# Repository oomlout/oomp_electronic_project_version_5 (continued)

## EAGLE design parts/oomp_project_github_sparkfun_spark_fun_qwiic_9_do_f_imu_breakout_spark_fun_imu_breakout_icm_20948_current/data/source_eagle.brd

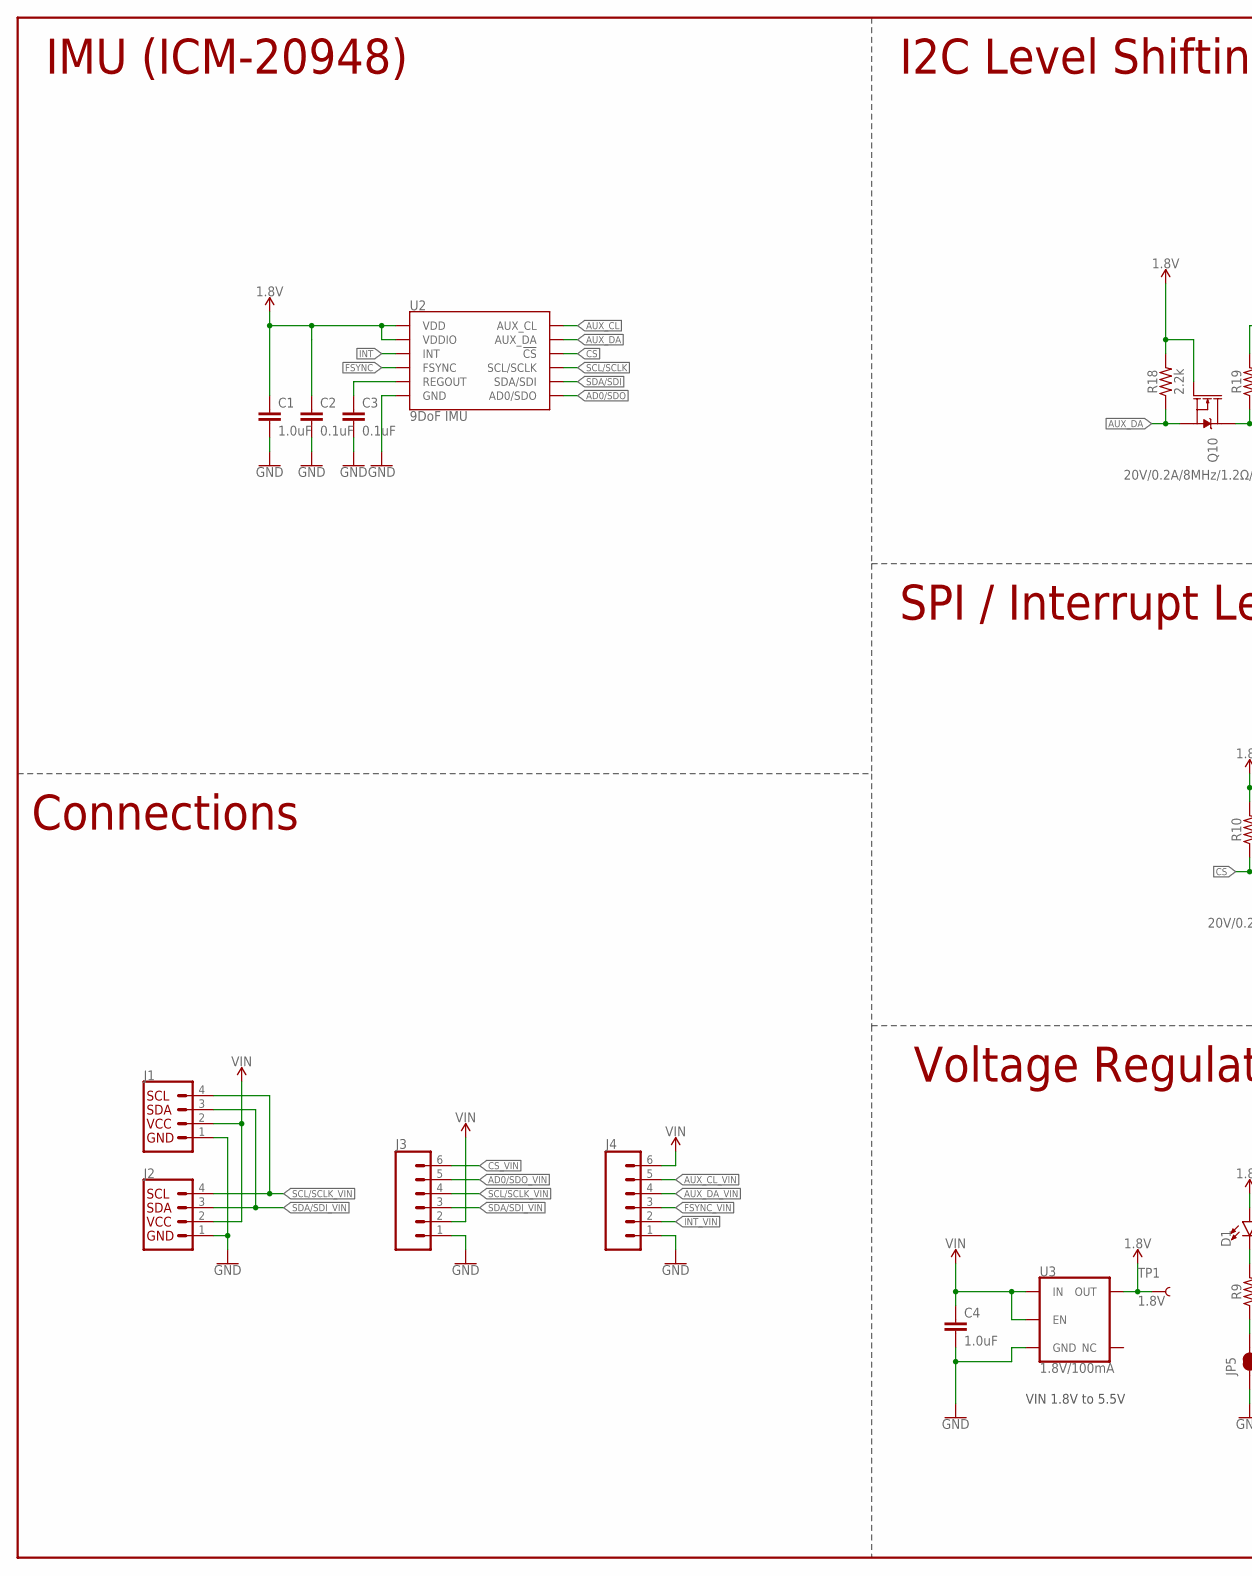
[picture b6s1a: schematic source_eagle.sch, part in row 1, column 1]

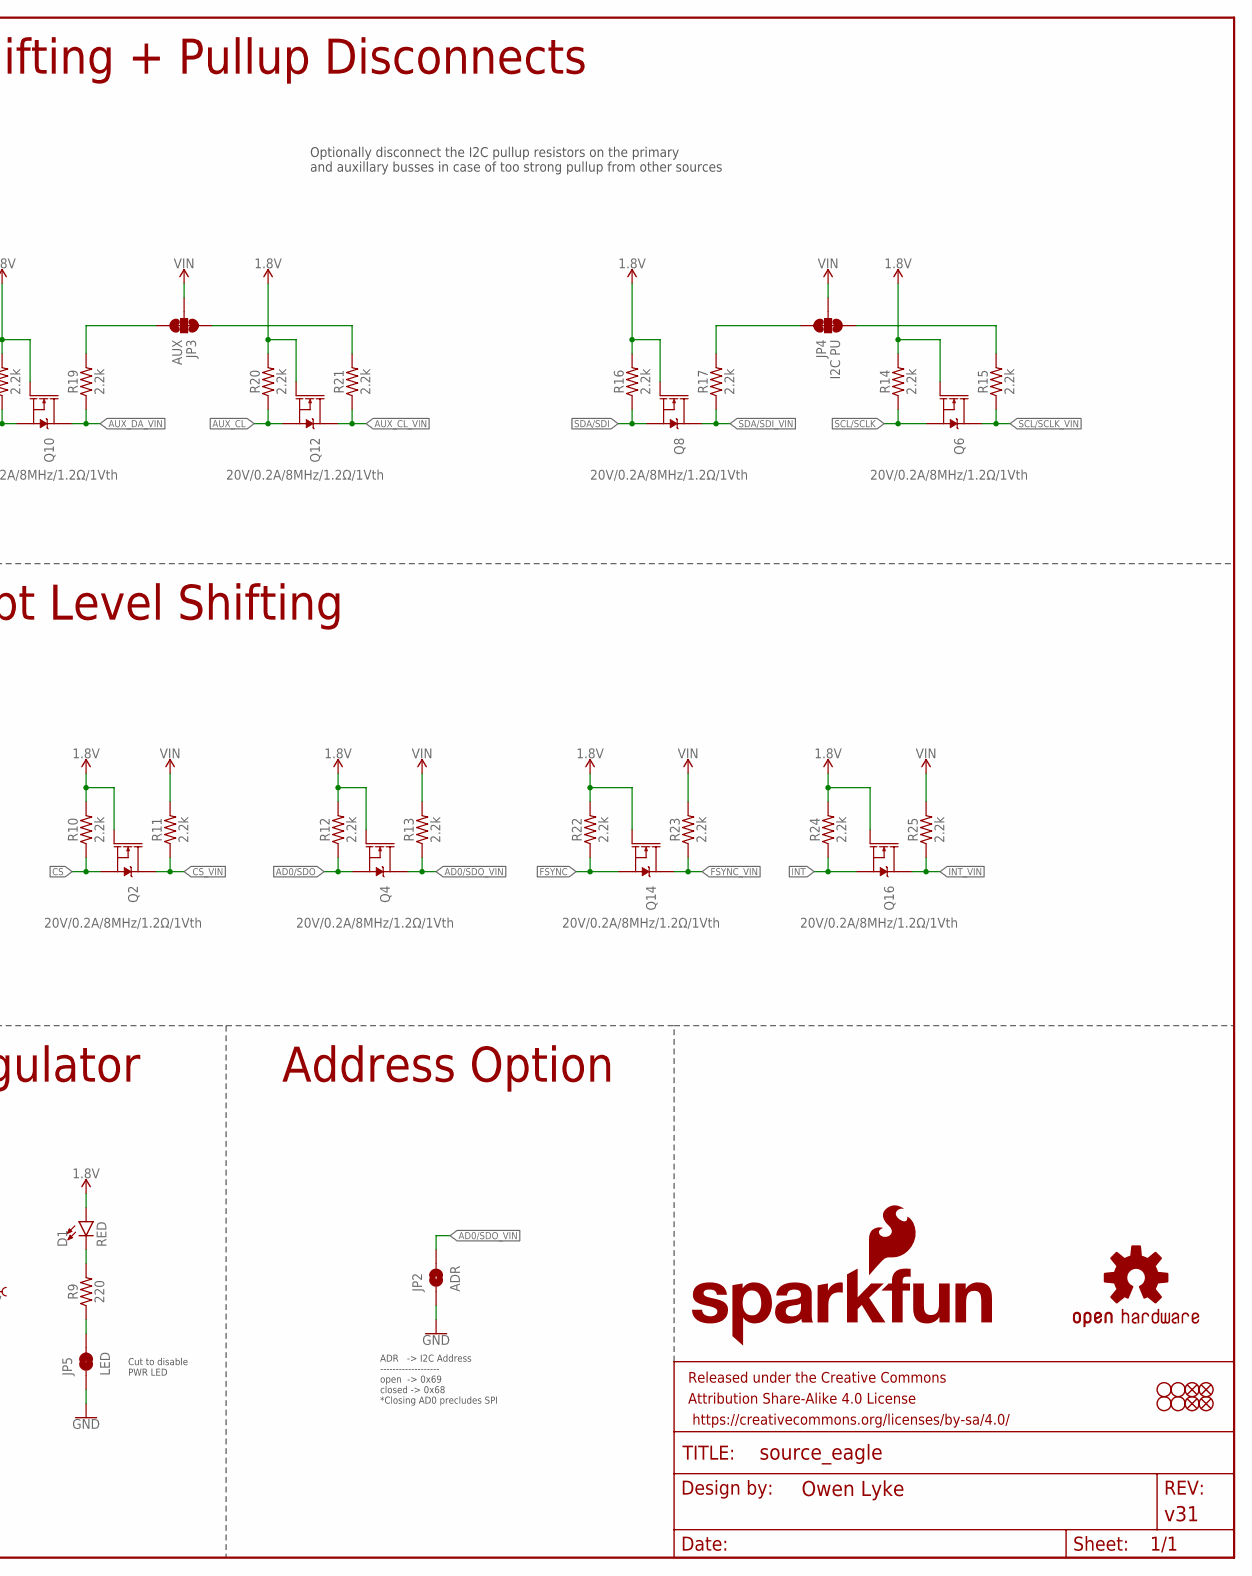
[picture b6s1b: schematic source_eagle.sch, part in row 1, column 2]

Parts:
C1, C4: 1.0uF; 0603
C2, C3: 0.1uF; 0603
D1: RED; LED-0603
FD1, FD2, FD3, FD4: FIDUCIAL1X2; FIDUCIAL-1X2
FRAME2: FRAME-LEDGER; CREATIVE_COMMONS
H1, H2, H3, H4: STAND-OFF
J1, J2: QWIIC_CONNECTORJS-1MM; JST04_1MM_RA
J3, J4: CONN_06NO_SILK_NO_POP; 1X06_NO_SILK
JP2: ADR; SMT-JUMPER_2_NO_SILK
JP3: AUX; SMT-JUMPER_3_2-NC_TRACE_SILK
JP4: I2C PU; SMT-JUMPER_3_2-NC_TRACE_SILK
JP5: LED; SMT-JUMPER_2_NC_TRACE_SILK
LOGO1: SFE_LOGO_NAME_FLAME.1_INCH; SFE_LOGO_NAME_FLAME_.1
LOGO2: OSHW-LOGOMINI; OSHW-LOGO-MINI
Q2, Q4, Q6, Q8, Q10, Q12, Q14, Q16: 20V/0.2A/8MHz/1.2Ω/1Vth; SOT-416FL
R9: 220; 0603
R10, R11, R12, R13, R14, R15, R16, R17, R18, R19, R20, R21, R22, R23, R24, R25: 2.2k; 0402-TIGHT
TP1: 1.8V; PAD.03X.03
U2: 9DoF IMU; QFN24-3X3
U3: 1.8V/100mA; SC70

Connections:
1.8V: C1.1, C2.1, D1.A, Q2.1 (G), Q4.1 (G), Q6.1 (G), Q8.1 (G), Q10.1 (G), Q12.1 (G), Q14.1 (G), Q16.1 (G), R10.2, R12.2, R14.2, R16.2, R18.2, R20.2, R22.2, R24.2, TP1.P$1, U2.8 (VDDIO), U2.13 (VDD), U3.5 (OUT)
!CS: Q2.2 (S), R10.1, U2.22 (!CS)
!CS!_VIN: J3.6, Q2.3 (D), R11.1
AD0/SDO: Q4.2 (S), R12.1, U2.9 (AD0/SDO)
AD0/SDO_VIN: J3.5, JP2.2, Q4.3 (D), R13.1
AUX_CL: Q12.2 (S), R20.1, U2.7 (AUX_CL)
AUX_CL_VIN: J4.5, Q12.3 (D), R21.1
AUX_DA: Q10.2 (S), R18.1, U2.21 (AUX_DA)
AUX_DA_VIN: J4.4, Q10.3 (D), R19.1
FSYNC: Q14.2 (S), R22.1, U2.11 (FSYNC)
FSYNC_VIN: J4.3, Q14.3 (D), R23.1
GND: C1.2, C2.2, C3.2, C4.2, J1.1, J2.1, J3.1, J4.1, JP2.1, JP5.1, U2.18 (GND), U2.20 (GND), U3.2 (GND)
INT: Q16.2 (S), R24.1, U2.12 (INT)
INT_VIN: J4.2, Q16.3 (D), R25.1
unnamed: C3.1, U2.10 (REGOUT)
unnamed: JP4.3, R15.2
unnamed: JP4.1, R17.2
unnamed: JP3.1, R21.2
unnamed: JP3.3, R19.2
unnamed: D1.C, R9.2
unnamed: JP5.2, R9.1
SCL/SCLK: Q6.2 (S), R14.1, U2.23 (SCL/SCLK)
SCL/SCLK_VIN: J1.4, J2.4, J3.4, Q6.3 (D), R15.1
SDA/SDI: Q8.2 (S), R16.1, U2.24 (SDA/SDI)
SDA/SDI_VIN: J1.3, J2.3, J3.3, Q8.3 (D), R17.1
VIN: C4.1, J1.2, J2.2, J3.2, J4.6, JP3.2, JP4.2, R11.2, R13.2, R23.2, R25.2, U3.1 (IN), U3.3 (EN)

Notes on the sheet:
VIN 1.8V to 5.5V
IMU (ICM-20948)
I2C Level Shifting + Pullup Disconnects
Connections
Voltage Regulator
SPI / Interrupt Level Shifting
ADR -> I2C Address ------------------- open -> 0x69 closed -> 0x68 *Closing AD0 precludes SPI
Optionally disconnect the I2C pullup resistors on the primary and auxillary busses in case of too strong pullup from other sources
Cut to disable PWR LED
Address Option

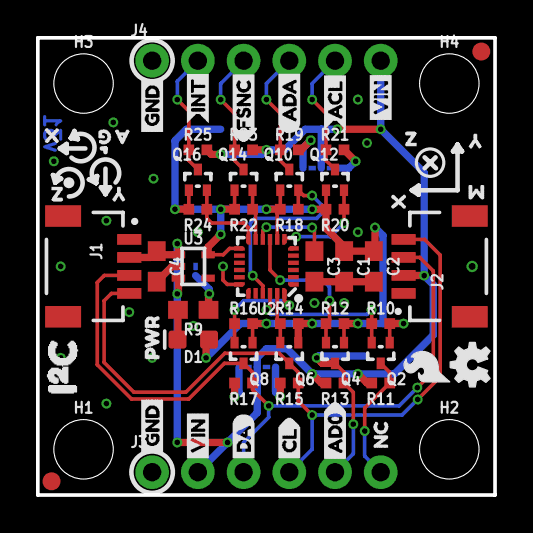
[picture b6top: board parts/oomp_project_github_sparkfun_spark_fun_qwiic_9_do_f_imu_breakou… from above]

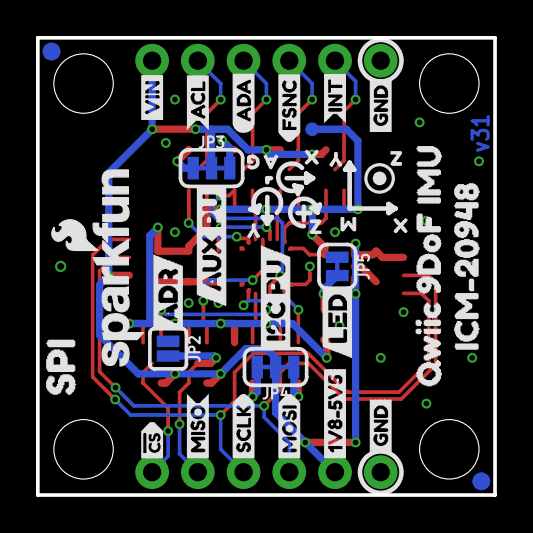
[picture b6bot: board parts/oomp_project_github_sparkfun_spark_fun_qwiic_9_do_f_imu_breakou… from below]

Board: 2 copper layers, 25.4 x 25.4 mm, 104 parts (36 on the bottom side), 26 nets.

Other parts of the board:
U$1, U$2, U$22, U$24: GND4
U$3: PWR0
U$4, U$21: INT3
U$5, U$20: FSNC2
U$6, U$19: ACL1
U$7, U$18: ADA0
U$8: MISO13
U$9: MOSI14
U$10: SCLK15
U$11: #CS16
U$12: 1V8#5V57
U$13, U$30, U$44: VIN5
U$14: NC17
U$15: CL4
U$16: DA2
U$17: AD012
U$23: ADR2
U$25: I2C_PU21
U$26: SPI19
U$27: AUX_PU24
U$28: SFE_LOGO_FLAME_.1
U$29: LED23
U$31: ICM#2094820
U$34, U$40, U$50, U$57: X0
U$35, U$41, U$51, U$58: Y1
U$36, U$42, U$52, U$59: Z2
U$37, U$60: G5
U$38, U$61: A4
U$39, U$49: M3
U$43: QWIIC_9DOF_IMU_0
U$45: I#C1

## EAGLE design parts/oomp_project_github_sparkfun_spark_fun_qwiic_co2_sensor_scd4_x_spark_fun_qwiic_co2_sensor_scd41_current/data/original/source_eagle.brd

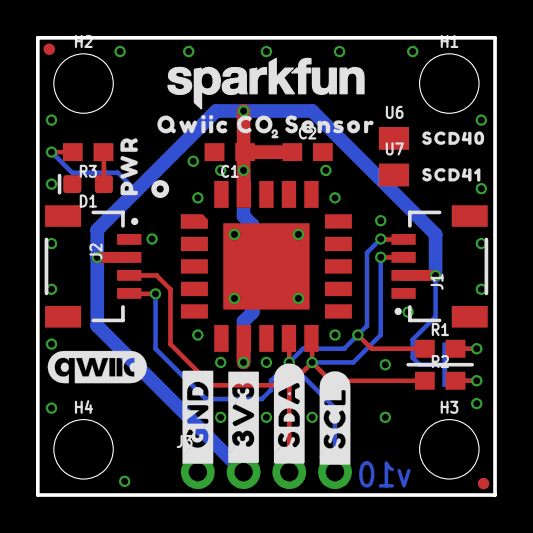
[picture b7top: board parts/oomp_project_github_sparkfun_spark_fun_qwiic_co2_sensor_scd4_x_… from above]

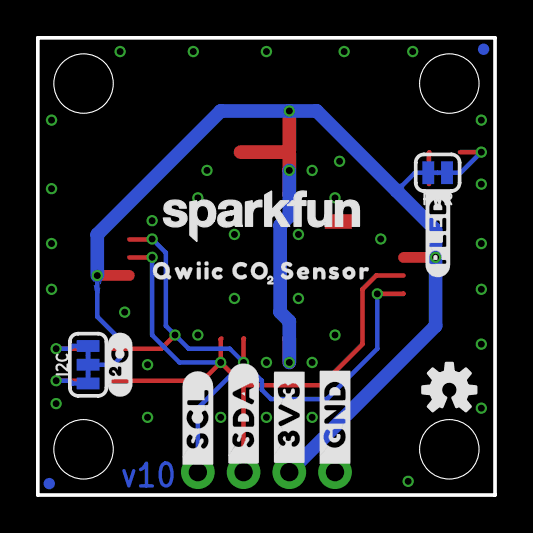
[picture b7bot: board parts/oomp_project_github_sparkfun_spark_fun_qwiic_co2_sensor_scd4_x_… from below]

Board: 2 copper layers, 25.4 x 25.4 mm, 49 parts (16 on the bottom side), 8 nets.

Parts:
C1: 0.1uF; 0603
C2: 4.7uF; 0603
D1: RED; LED-0603
FD1, FD2, FD3, FD4: FIDUCIALUFIDUCIAL; FIDUCIAL-MICRO
FRAME1: FRAME-LETTER; CREATIVE_COMMONS
H1, H2, H3, H4: STAND-OFF
I2C: I2C; SMT-JUMPER_3_2-NC_TRACE_SILK
J1, J2: QWIIC_RA; JST04_1MM_RA
J3: PTH; 1X04_NO_SILK
LOGO1: QWIIC_LOGO_CONNECTOR; QWIIC_5.5MM
LOGO2: OSHW-LOGOS; OSHW-LOGO-S
LOGO3: SFE_LOGO_NAME_FLAMEBLANK; BLANK
PWR: PWR; SMT-JUMPER_2_NC_TRACE_SILK
R1, R2: 2.2k; 0603
R3: 4.7k; 0603
U1: SCD40/1; SCD4X
U6: SCD40; PRODUCT_IDENT_NO_NO-SILK
U7: SCD41; PRODUCT_IDENT_PASTE_NO-SILK
U$1, U$18: #_GND#14
U$2, U$19: #_3V3#15
U$3, U$20: #_SDA#15
U$4, U$21: #_SCL#16
U$5, U$12: SFE_LOGO_NAME_.1
U$6: SCD414140404021
U$7: SCD40414140404022
U$8, U$13: QWIIC_CO0
U$9, U$14: SENSOR0
U$10, U$15: 20
U$11: SFE_LOGO_FLAME_STOP_.1
U$16: #PLED#21
U$17: #I�C#0
U$22: ORDERING_INSTRUCTIONS
U$23: PWR0

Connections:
3.3V: C1.1, C2.1, I2C.2, J1.2, J2.2, J3.2, PWR.2, U1.7, U1.19
GND: C1.2, C2.2, D1.C, J1.1, J2.1, J3.1, U1.6, U1.20, U1.CP
unnamed: I2C.1, R2.2
unnamed: I2C.3, R1.2
unnamed: PWR.1, R3.2
unnamed: D1.A, R3.1
SCL: J1.4, J2.4, J3.4, R1.1, U1.9
SDA: J1.3, J2.3, J3.3, R2.1, U1.10
